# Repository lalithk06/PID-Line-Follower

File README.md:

# 🤖 ESP32 Line Follower Robot — Hardware Design
*A compact and efficient line follower robot built using the ESP32*

## Demo

This project showcases the schematic and PCB design of a reliable line follower robot capable of high-speed tracking with stable power delivery and clean motor control. It is designed as a practical exploration of real-world embedded hardware development and PCB design workflows.

---

## 📂 Repository Structure
```
PID-Line-Follower
│
├── Firmware
│   └── Arduino_Code
│
├── Hardware
│   ├── Images
│   ├── Schematic
│   ├── Datasheet
│   └── Pin_Mapping
│
├── README.md
└── .gitignore
```
---

## Working Principle

- The ESP32 DevKit (38-pin) acts as the main controller.
- An 8-channel IR sensor array detects the line:
  - 6 sensors operate in analog mode for precise position tracking.
  - 2 sensors operate in digital mode for edge detection.
- The TB6612FNG motor driver controls two DC motors with efficient PWM-based speed regulation.
- A LM2596 buck converter steps down the battery voltage to provide a stable **3.3V rail** for the ESP32 and logic circuitry.
- Two push buttons allow:
  - Calibration mode – tune sensor thresholds.
  - Mode selection – switch between operating behaviors.
- Decoupling capacitors and a ground plane ensure noise reduction and power stability.

---

## 🎯 Objective

To design and develop a robust hardware platform for a line follower robot that demonstrates:

- Proper power architecture  
- Motor driver integration  
- Mixed analog/digital sensing  
- Clean PCB layout practices  
- Expandable embedded design  

---

## Hardware Overview

| No. | Component | Role |
|------|------------|--------|
| 1 | ESP32 DevKit (38-pin) | Main microcontroller with Wi-Fi & BLE |
| 2 | TB6612FNG | Dual motor driver |
| 3 | LM2596 Buck Converter | Efficient voltage regulation |
| 4 | IR Sensor Array (8-channel) | Line detection |
| 5 | Push Buttons (2x) | Calibration & mode selection |
| 6 | Battery Input + Slide Switch | Power control |
| 7 | Capacitors | Filtering & decoupling |
| 8 | Mounting Holes | Mechanical stability |

---

## Power Architecture

**Battery → Slide Switch → LM2596 Buck → 3.3V Rail**

Design considerations:

✅ Wide power traces for motor current  
✅ Dedicated ground plane  
✅ Local decoupling near driver and ESP32  
✅ Separate motor and logic routing where possible  

---

## Firmware

The robot firmware is written for the ESP32 using the Arduino framework.

Key features of the control software:

• Multi-sensor line detection  
• Adaptive speed control  
• PID-based steering correction  
• Calibration routines for sensor tuning  

Firmware source code is available in the `Firmware` directory.

---

## 📷 Preview

### 🖼️ Schematic  

### 📐 PCB Layout  

### 🧊 3D View  

---

## Key Features

✅ Stable buck-regulated power supply  
✅ High-efficiency TB6612FNG motor control  
✅ Mixed analog + digital sensor interface  
✅ Compact 2-layer PCB  
✅ Ground plane for noise reduction  
✅ Designed following practical PCB routing guidelines  

---

## Design Notes

- Motor traces are sized to handle higher current.
- Ground return paths are optimized using copper pour.
- Mounting holes are included for chassis integration.
- Connectors are placed for easy wiring and maintenance.

---

## Future Improvements

- PID tuning for smoother tracking  
- Encoder-based speed feedback  
- Bluetooth / Wi-Fi telemetry  
- Battery voltage monitoring  
- On-board charging circuit  
- Custom buck stage instead of module  
- Fully integrated motor + sensor board  

---

## 📚 Learning Outcomes

This project helped strengthen understanding of:

- Power electronics in embedded systems  
- PCB stackup and routing  
- Grounding strategies  
- Motor driver layout considerations  
- Hardware debugging practices

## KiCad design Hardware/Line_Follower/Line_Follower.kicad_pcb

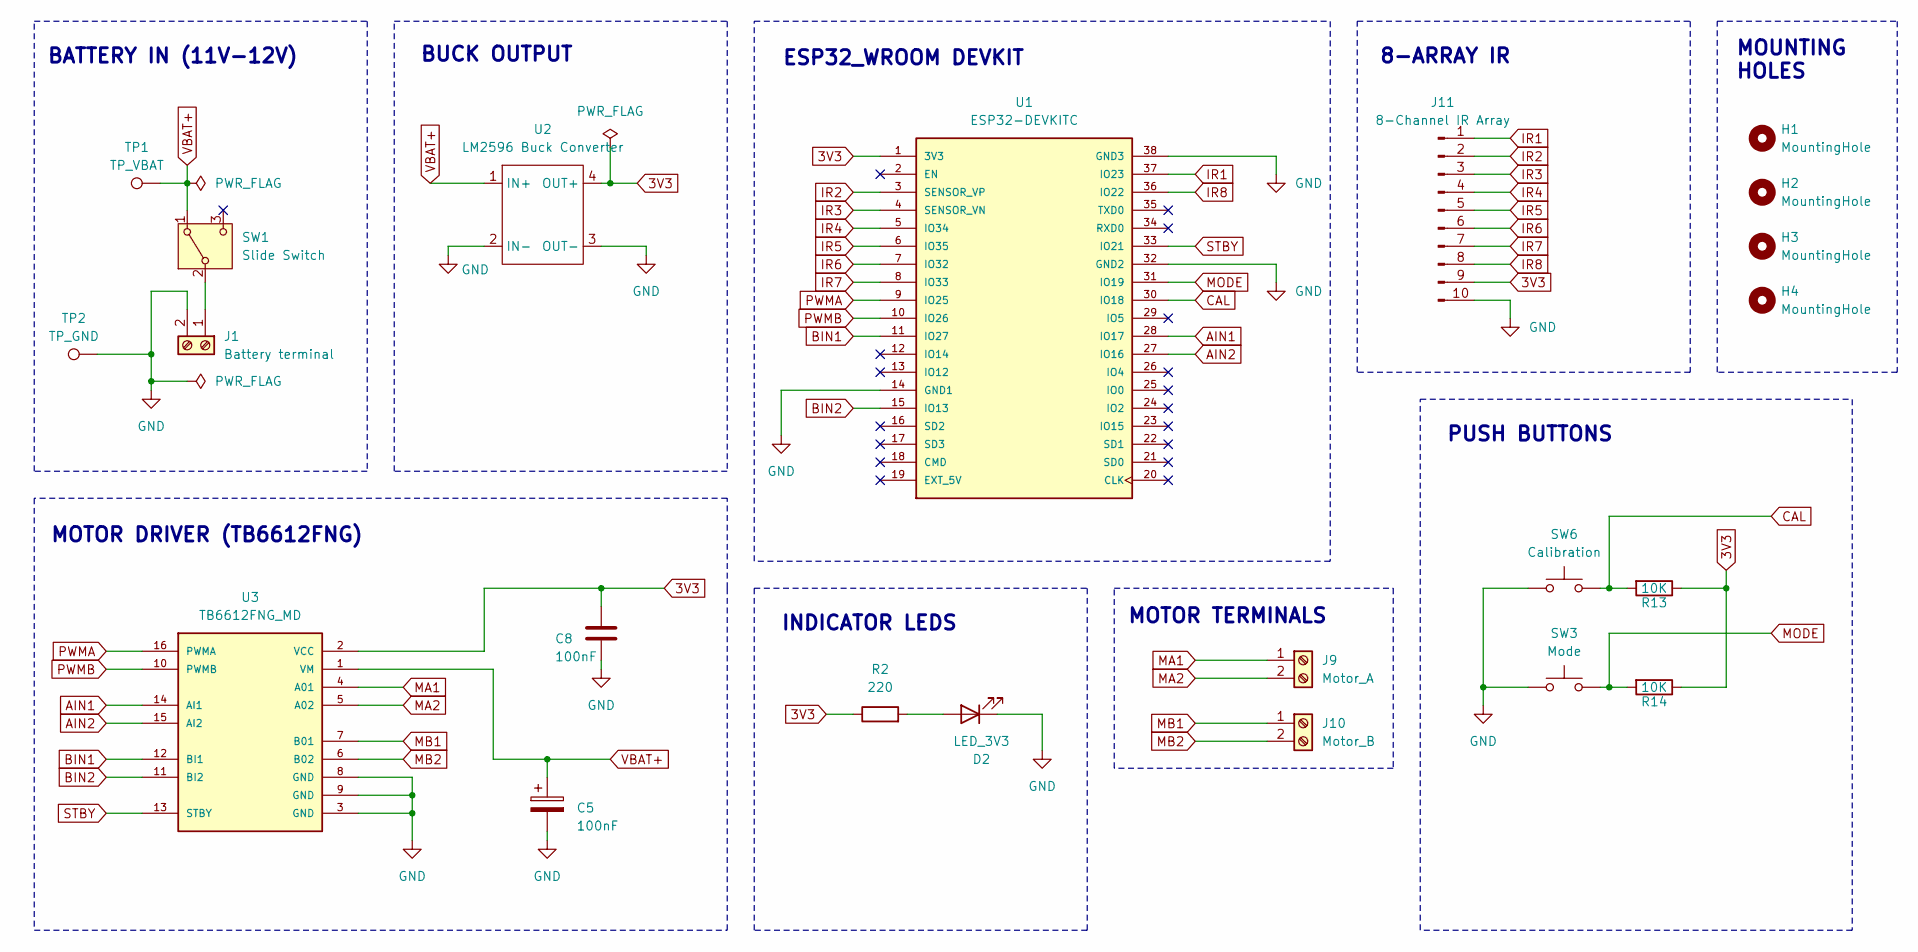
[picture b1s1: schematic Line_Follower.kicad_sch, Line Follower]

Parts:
C5, C8: 100nF; C320C
D2: LED_3V3; LED_D5.0mm
H1, H2, H3, H4: MountingHole; MountingHole_3.2mm_M3
J1: Battery terminal; CUI_TB007-508-02BE
J9: Motor_A; CUI_TB007-508-02BE
J10: Motor_B; CUI_TB007-508-02BE
J11: 8-Channel IR Array; PinHeader_1x10_P2.54mm_Vertical
R2: 220; R_Axial_DIN0207_L6.3mm_D2.5mm_P10.16mm_Horizontal
R13, R14: 10K; R_Axial_DIN0207_L6.3mm_D2.5mm_P10.16mm_Horizontal
SW1: Slide Switch; SW_Slide-03_Wuerth-WS-SLTV_10x2.5x6.4_P2.54mm
SW3: Mode; SW_PUSH_6mm
SW6: Calibration; SW_PUSH_6mm
TP1: TP_VBAT; TestPoint_Pad_2.0x2.0mm
TP2: TP_GND; TestPoint_Pad_2.0x2.0mm
U1: ESP32-DEVKITC; MODULE_ESP32-DEVKITC; PARTREV N/A
U2: LM2596 Buck Converter; LM2596_Buck_Module
U3: TB6612FNG_MD; TB6612FNG_Driver

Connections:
3V3: C8.1, J11.9, R2.1, R13.1, R14.1, U1.1 (3V3), U2.4 (OUT+), U3.2 (VCC)
AIN1: U1.28 (IO17), U3.14 (AI1)
AIN2: U1.27 (IO16), U3.15 (AI2)
BIN1: U1.11 (IO27), U3.12 (BI1)
BIN2: U1.15 (IO13), U3.11 (BI2)
CAL: R13.2, SW6.2, U1.30 (IO18)
GND: C5.2, C8.2, D2.1 (K), J1.2, J11.10, SW3.1, SW6.1, TP2.1, U1.14 (GND1), U1.32 (GND2), U1.38 (GND3), U2.2 (IN-), U2.3 (OUT-), U3.3 (GND), U3.8 (GND), U3.9 (GND)
IR1: J11.1, U1.37 (IO23)
IR2: J11.2, U1.3 (SENSOR_VP)
IR3: J11.3, U1.4 (SENSOR_VN)
IR4: J11.4, U1.5 (IO34)
IR5: J11.5, U1.6 (IO35)
IR6: J11.6, U1.7 (IO32)
IR7: J11.7, U1.8 (IO33)
IR8: J11.8, U1.36 (IO22)
MA1: J9.1, U3.4 (A01)
MA2: J9.2, U3.5 (A02)
MB1: J10.1, U3.7 (B01)
MB2: J10.2, U3.6 (B02)
MODE: R14.2, SW3.2, U1.31 (IO19)
unnamed: D2.2 (A), R2.2
unnamed: J1.1, SW1.2 (B)
PWMA: U1.9 (IO25), U3.16 (PWMA)
PWMB: U1.10 (IO26), U3.10 (PWMB)
STBY: U1.33 (IO21), U3.13 (STBY)
VBAT+: C5.1, SW1.1 (A), TP1.1, U2.1 (IN+), U3.1 (VM)

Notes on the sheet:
BUCK OUTPUT
8-ARRAY IR
MOUNTING HOLES
MOTOR TERMINALS
INDICATOR LEDS
BATTERY IN (11V-12V)
PUSH BUTTONS
MOTOR DRIVER (TB6612FNG)
ESP32_WROOM DEVKIT

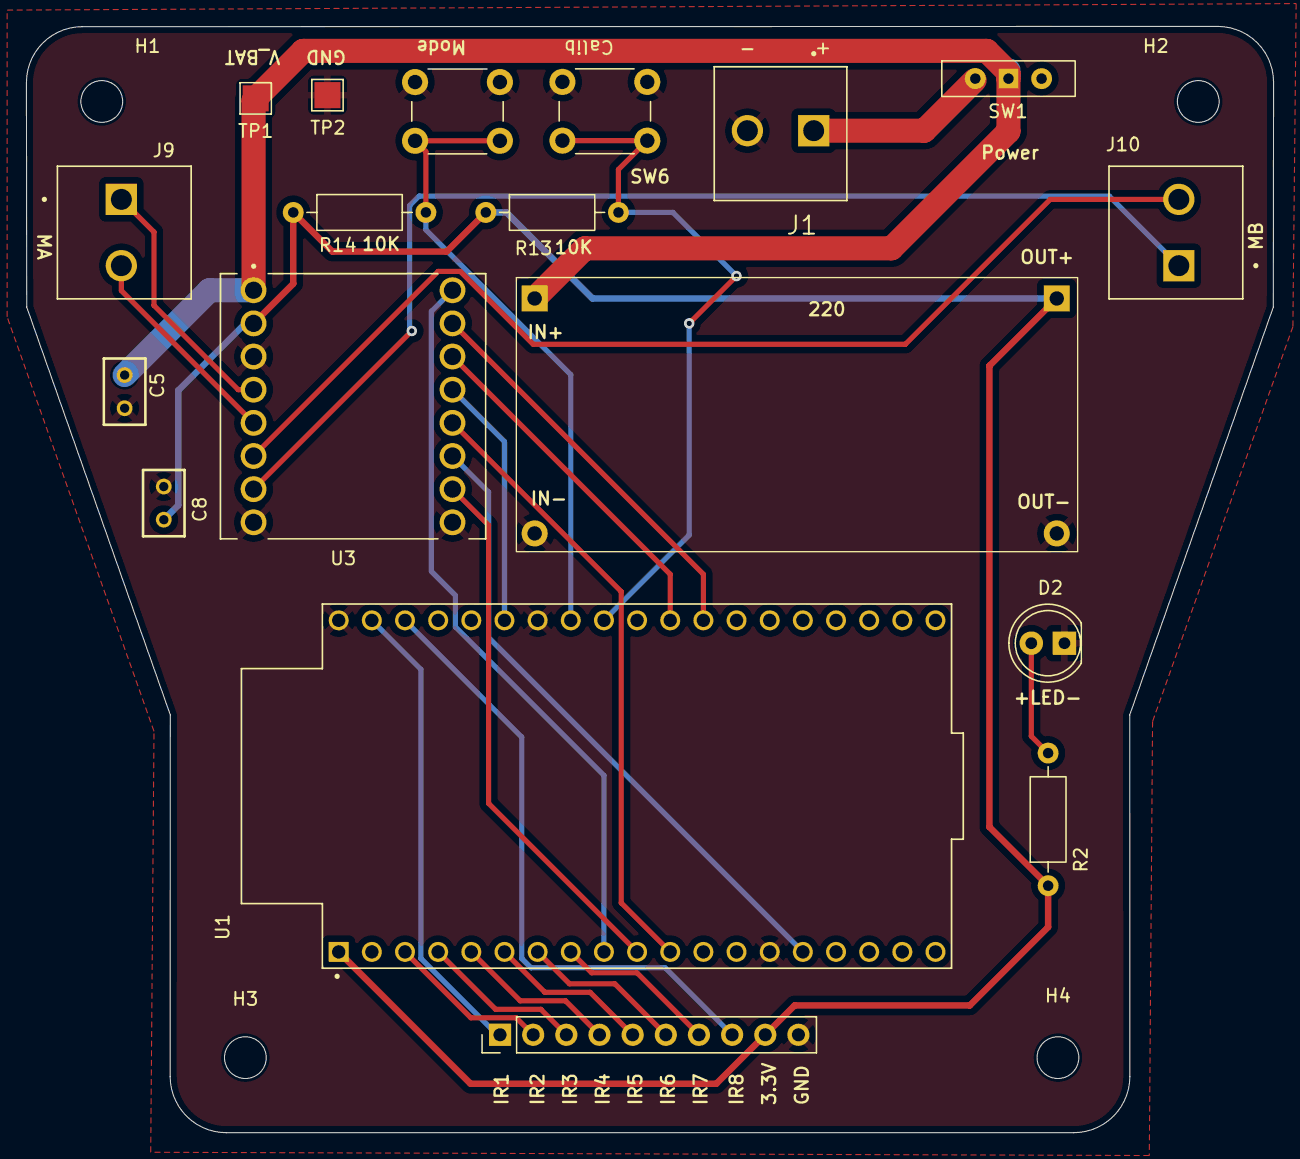
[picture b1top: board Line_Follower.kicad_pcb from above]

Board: 2 copper layers, 95.5 x 84.7 mm, 22 parts (0 on the bottom side), 26 nets.

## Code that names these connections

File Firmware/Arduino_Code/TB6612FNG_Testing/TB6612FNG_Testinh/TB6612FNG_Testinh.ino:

// ========= MOTOR PINS =========
#define PWMA 25
#define PWMB 26
#define AIN1 17
#define AIN2 16
#define BIN1 27
#define BIN2 13
#define STBY 21

// ========= PWM SETTINGS =========
#define freq 1000
#define resolution 8

#define channelA 0
#define channelB 1

int speedMotor = 180; // 0-255

void setup() {

  pinMode(AIN1, OUTPUT);
  pinMode(AIN2, OUTPUT);
  pinMode(BIN1, OUTPUT);
  pinMode(BIN2, OUTPUT);
  pinMode(STBY, OUTPUT);

  digitalWrite(STBY, HIGH); // Wake driver

  // PWM setup
  ledcSetup(channelA, freq, resolution);
  ledcAttachPin(PWMA, channelA);

  ledcSetup(channelB, freq, resolution);
  ledcAttachPin(PWMB, channelB);
}

// ================= MOTOR FUNCTIONS =================

void forward() {

  digitalWrite(AIN1, HIGH);
  digitalWrite(AIN2, LOW);

  digitalWrite(BIN1, HIGH);
  digitalWrite(BIN2, LOW);

  ledcWrite(channelA, speedMotor);
  ledcWrite(channelB, speedMotor);
}

void backward() {

  digitalWrite(AIN1, LOW);
  digitalWrite(AIN2, HIGH);

  digitalWrite(BIN1, LOW);
  digitalWrite(BIN2, HIGH);

  ledcWrite(channelA, speedMotor);
  ledcWrite(channelB, speedMotor);
}

void left() {

  ledcWrite(channelA, 80);   // slow left motor
  ledcWrite(channelB, 200);  // fast right motor

  digitalWrite(AIN1, HIGH);
  digitalWrite(AIN2, LOW);

  digitalWrite(BIN1, HIGH);
  digitalWrite(BIN2, LOW);
}

void right() {

  ledcWrite(channelA, 200);
  ledcWrite(channelB, 80);

  digitalWrite(AIN1, HIGH);
  digitalWrite(AIN2, LOW);

  digitalWrite(BIN1, HIGH);
  digitalWrite(BIN2, LOW);
}

void stopMotor() {

  ledcWrite(channelA, 0);
  ledcWrite(channelB, 0);
}

// ================= TEST LOOP =================

void loop() {

  forward();
  delay(3000);

  stopMotor();
  delay(1000);

  backward();
  delay(3000);

  stopMotor();
  delay(1000);

  left();
  delay(2000);

  right();
  delay(2000);

  stopMotor();
  delay(4000);
}

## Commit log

2026-02-08 Schematics updated
2026-02-08 PCB updated
2026-02-08 Schematic edited
2026-02-08 Net classes assigned
2026-02-08 Footprint added, PCB aligned
2026-02-09 PCB edge cuts designed
2026-02-10 PCB edited
2026-02-10 3D models added
2026-02-11 3D model
2026-02-11 Routing started
2026-02-11 Routing done
2026-02-11 Routing optimised
2026-02-12 Routing modified
2026-02-13 File updated
2026-02-14 Capacitors removed
2026-02-14 Gerber created
2026-02-14 manufacturing files
2026-02-14 README added
2026-02-14 README edited
2026-02-14 Images added
2026-03-14 Plot updated
2026-03-14 Images uploaded
2026-03-14 Removed manufacturing and CAD files
2026-03-14 Image folder created
2026-03-14 Images folder reorganised
2026-03-14 Updated README.m
2026-03-14 Reconstructed repo firmware and hardware folders
2026-03-14 folders reorganised
2026-03-14 Firmware updated
2026-03-14 Folder name updated
2026-03-14 readme updated
2026-03-14 Demo uploaded
